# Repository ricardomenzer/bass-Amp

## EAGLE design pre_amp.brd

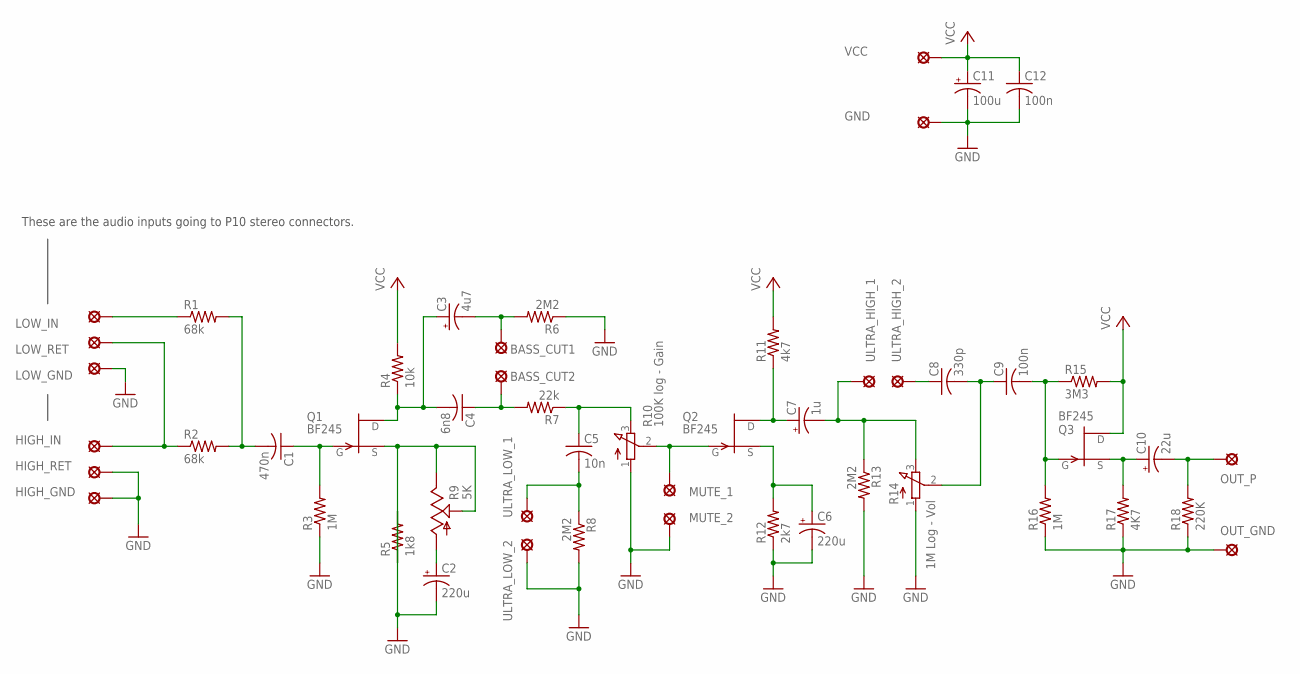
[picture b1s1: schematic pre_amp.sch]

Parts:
BASS_CUT1, BASS_CUT2: MCS08
C1: 470n; C050-035X075
C2: 220u; E5-8,5
C3: 4u7; E2,5-6
C4: 6n8; C050-030X075
C5: 10n; C050-030X075
C6: 220u; E3,5-8
C7: 1u; E2,5-6
C8: 330p; C050-025X075
C9, C12: 100n; C075-042X103
C10: 22u; E2-5
C11: 100u; E3,5-10
GND: MCS08
HIGH_GND: MCS08
HIGH_IN: MCS08
HIGH_RET: MCS08
LOW_GND: MCS08
LOW_IN: MCS08
LOW_RET: MCS08
MUTE_1, MUTE_2: MCS08
OUT_GND: MCS08
OUT_P: MCS08
Q1, Q2, Q3: BF245; TO92
R1, R2: 68k; 0204/7
R3, R16: 1M; 0204/7
R4: 10k; 0204/7
R5: 1k8; 0207/10
R6, R8, R13: 2M2; 0204/7
R7: 22k; 0204/7
R9: 5K; CA6V
R10: 100K log - Gain; 3RP/1610N
R11: 4k7; 0204/7
R12: 2k7; 0204/7
R14: 1M Log - Vol; 3RP/1610N
R15: 3M3; 0204/7
R17: 4K7; 0204/7
R18: 220K; 0204/7
ULTRA_HIGH_1, ULTRA_HIGH_2: MCS08
ULTRA_LOW_1, ULTRA_LOW_2: MCS08
VCC: MCS08

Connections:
GND: C2.-, C6.-, C11.-, C12.2, GND.MP, HIGH_GND.MP, HIGH_RET.MP, LOW_GND.MP, MUTE_2.MP, OUT_GND.MP, R3.1, R5.2, R6.1, R8.2, R10.1 (A), R12.1, R13.2, R14.1 (A), R16.1, R17.1, R18.1, ULTRA_LOW_2.MP
unnamed: C1.2, R1.2, R2.2
unnamed: C1.1, Q1.3 (G), R3.2
unnamed: C3.+, C4.2, Q1.1 (D), R4.1
unnamed: Q1.2 (S), R5.1, R9.E, R9.S
unnamed: C2.+, R9.A
unnamed: LOW_IN.MP, R1.1
unnamed: HIGH_IN.MP, LOW_RET.MP, R2.1
unnamed: BASS_CUT1.MP, C3.-, R6.2
unnamed: BASS_CUT2.MP, C4.1, R7.2
unnamed: C5.1, R7.1, R10.3 (E)
unnamed: C5.2, R8.1, ULTRA_LOW_1.MP
unnamed: C7.+, Q2.1 (D), R11.1
unnamed: C6.+, Q2.2 (S), R12.2
unnamed: C7.-, R13.1, R14.3 (E), ULTRA_HIGH_1.MP
unnamed: MUTE_1.MP, Q2.3 (G), R10.2 (S)
unnamed: C8.2, C9.1, R14.2 (S)
unnamed: C8.1, ULTRA_HIGH_2.MP
unnamed: C9.2, Q3.3 (G), R15.1, R16.2
unnamed: C10.+, Q3.2 (S), R17.2
unnamed: C10.-, OUT_P.MP, R18.2
VCC: C11.+, C12.1, Q3.1 (D), R4.2, R11.2, R15.2, VCC.MP

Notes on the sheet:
These are the audio inputs going to P10 stereo connectors.

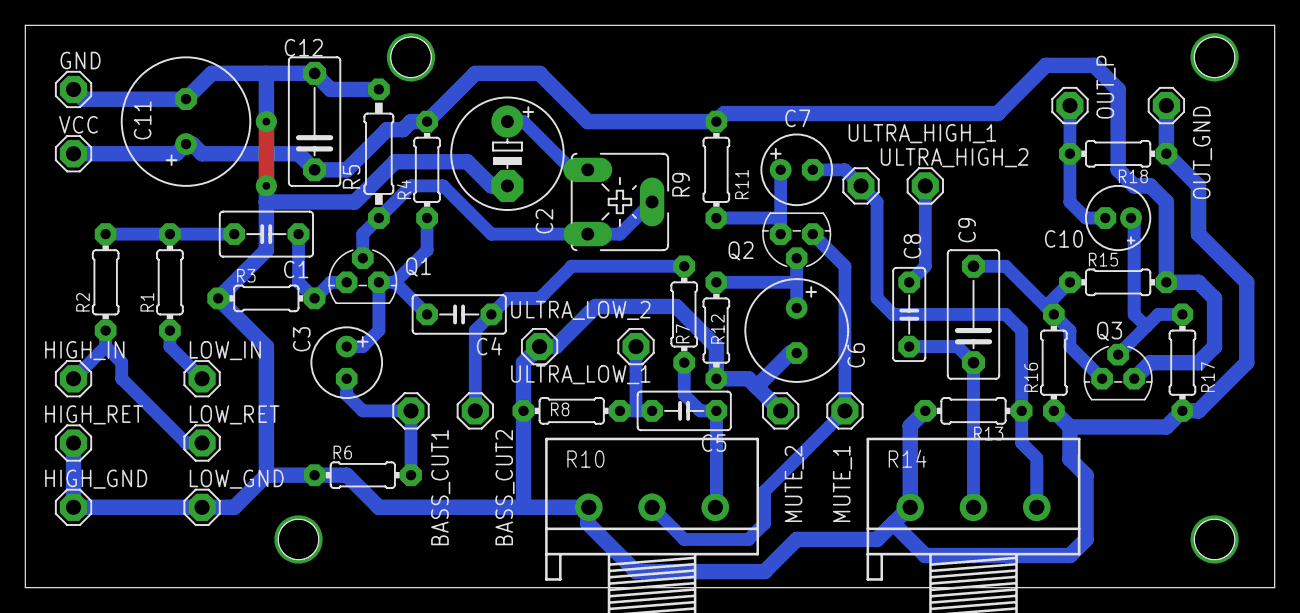
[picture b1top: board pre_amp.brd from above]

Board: 2 copper layers, 98.7 x 44.4 mm, 51 parts (0 on the bottom side), 22 nets.

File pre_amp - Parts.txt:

Partlist

Exported from pre_amp.sch at 12/09/2015 00:15:36

EAGLE Version 7.2.0 Copyright (c) 1988-2014 CadSoft

Assembly variant: 

Part         Value           Device          Package      Library        Sheet

BASS_CUT1    MCS08           MCS08           MCS08        solpad         1
BASS_CUT2    MCS08           MCS08           MCS08        solpad         1
C1           470n            C-US050-035X075 C050-035X075 resistor       1
C2           220u            CPOL-USE3.5-8   E3,5-8       resistor       1
C3           4u7             CPOL-USE2.5-6   E2,5-6       resistor       1
C4           6n8             C-US375-203X418 C375-203X418 rcl            1
C5           10n             C-US050-030X075 C050-030X075 rcl            1
C6           220u            CPOL-USE3.5-8   E3,5-8       resistor       1
C7           1u              CPOL-USE2.5-6   E2,5-6       rcl            1
C8           330p            C-US375-203X418 C375-203X418 rcl            1
C9           100n            C-US075-042X103 C075-042X103 rcl            1
C10          22u             CPOL-USE2-5     E2-5         rcl            1
C11          100u            CPOL-USE3.5-10  E3,5-10      rcl            1
C12          100n            C-US075-042X103 C075-042X103 rcl            1
GND          MCS08           MCS08           MCS08        solpad         1
HIGH_GND     MCS08           MCS08           MCS08        solpad         1
HIGH_IN      MCS08           MCS08           MCS08        solpad         1
HIGH_RET     MCS08           MCS08           MCS08        solpad         1
LOW_GND      MCS08           MCS08           MCS08        solpad         1
LOW_IN       MCS08           MCS08           MCS08        solpad         1
LOW_RET      MCS08           MCS08           MCS08        solpad         1
MUTE_1       MCS08           MCS08           MCS08        solpad         1
MUTE_2       MCS08           MCS08           MCS08        solpad         1
OUT_GND      MCS08           MCS08           MCS08        solpad         1
OUT_P        MCS08           MCS08           MCS08        solpad         1
Q1           BF245           BF245           TO92         transistor-fet 1
Q2           BF245           BF245           TO92         transistor-fet 1
Q3           BF245           BF245           TO92         transistor-fet 1
R1           68k             R-US_0204/7     0204/7       resistor       1
R2           68k             R-US_0204/7     0204/7       resistor       1
R3           1M              R-US_0204/7     0204/7       resistor       1
R4           10k             R-US_0204/7     0204/7       resistor       1
R5           1k8             R-US_0204/7     0204/7       resistor       1
R6           2M2             R-US_0204/7     0204/7       resistor       1
R7           22k             R-US_0204/7     0204/7       resistor       1
R8           2M2             R-US_0204/7     0204/7       resistor       1
R9           5K              TRIM_US-CA6V    CA6V         pot            1
R10          100K log - Gain 3RP/1610N       3RP/1610N    pot            1
R11          4k7             R-US_0204/7     0204/7       resistor       1
R12          2k7             R-US_0204/7     0204/7       resistor       1
R13          2M2             R-US_0204/7     0204/7       resistor       1
R14          1M Log - Vol    3RP/1610N       3RP/1610N    pot            1
R15          3M3             R-US_0204/7     0204/7       resistor       1
R16          1M              R-US_0204/7     0204/7       resistor       1
R17          4K7             R-US_0204/7     0204/7       resistor       1
R18          220K            R-US_0204/7     0204/7       resistor       1
ULTRA_HIGH_1 MCS08           MCS08           MCS08        solpad         1
ULTRA_HIGH_2 MCS08           MCS08           MCS08        solpad         1
ULTRA_LOW_1  MCS08           MCS08           MCS08        solpad         1
ULTRA_LOW_2  MCS08           MCS08           MCS08        solpad         1
VCC          MCS08           MCS08           MCS08        solpad         1

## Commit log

2015-09-12 [#1] Schematic drawing
    First drawing of the schematics.
2015-09-12 [#1] Improvements and fixes
    Fixes ERC check errors:
    R9 value set;
    Approved FRAME have no value.
    Better positioning some labels and texts.
2015-09-12 [#1] BOM
    Generated Bill of Materials file.
2015-09-12 [#1] Update component package
    Update component package.
2015-09-12 [#1] Create board file
    Create board file for the pre amplifier.
2015-09-15 [#1] PCB layout
